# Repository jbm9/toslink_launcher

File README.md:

# TOSLink Launcher

Author: <josh@joshisanerd.com>

License: CC0 / Public Domain

This is a quick-and-dirty PCB mounted TOSLink launcher, which can
couple an SMD LED into a TOSLINK optical cable.  The project includes
both the FreeCAD model and a KiCad demo project (which you can pull
the library/module/STP file out of and into your own setup to use
these.)

There is also an included STL file, but see below on the settings it
was printed with.

## Background
 
TOSLink is a really handy fiber optic cable: you can buy them easily,
reasonably cheaply, and in various lengths.  They are meant for audio,
but they're just flexible lightpipes at the end of the day.

You can buy TOSLink connectors that solder onto PCBs, but they only
come with red LEDs (which is used in the audio application).  If you
want to put arbitrary colors through them, it gets complicated.  So, I
decided to make a little connector that would let me mount a TOSLink
cable over an arbitrary surface mount LED.

## Limitations of included STL file

The STL included here assumes that your printer needs 0.2mm of
fudge-factor on each side to get good results on interior holes.  This
has been the case on both of my FDM printers, but it's probably going
to be suboptimal on SLA (or a particularly well-tuned FDM printer).

It is designed to put the end of the fiber cable 0.7mm above the
surface it's bolted down to.

## Mounting this on a PCB

The mounting arrangement for this is two holes 17mm apart.  I
recommend using 5mm drill hits for these, as you will need to align
the fiber optics perfectly with the LED underneath it.  To do this,
you want to move the connector around a little after it's mounted to
the PCB.  Putting M3 screws through a 5mm hole lets you move up to 1mm
in any direction from center, which should be good enough.

The recommended PCB footprint is an 8mm circle around those M5s, and a
13mm circle about your LED.  (I never claimed this was a
space-efficient footprint…)

## The KiCad demo project

There is a KiCad demo project in toslink_launcher_test.  Opening this
up in KiCad, then going to pcbnew, you should be able to do a 3D view
and see the parts rendered there.

The KiCad demo project includes a separate README.txt which describes
how to import all this into your own KiCad.

## The FreeCAD model

The model was developed in Ubuntu 20.04's distribution of FreeCAD, so
it's an ancient v0.18.4 file.  Apologies if it doesn't actually open
properly in newer versions.

This is a spreadsheet-driven FreeCAD file: if you need to adjust the
squeeze-out fudge factor, or the height of the LED, etc, you can open
the Spreadsheet in the file, tweak the values in that spreadsheet
(don't forget to include “mm” or FreeCAD will have a pedantic little
fit), and it should update the model.  You can then Activate the
“TOSLink Launcher001” Body object by double-clicking on it, and then
File > Export, and type in “toslink_launcher_foo.stl” (you also need
to add the STL there, FreeCAD's great).

This is also a reasonable starting point for the TOSLink connector;
there are precious few models using it, so hopefully this is a good
jumping-off point for anyone else who wants to use these cables for
alternate purposes.

## Further support

Please find someone to assist you with this: unfortunately, I don't
really have the time to help people with it.  This project is being
released more as a starting point for others than as a product in and
of itself.

## Contents:

* README.md: this file
* toslink_launcher.FCStd: FreeCAD v0.18.4 model
* toslink_launcher_v3.stl: STL of the actual launcher
* toslink_launcher_test/: KiCad demo project for the launcher
* imgs/: Images.

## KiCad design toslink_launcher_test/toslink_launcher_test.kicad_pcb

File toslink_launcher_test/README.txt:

# TOSLINK Launcher Example:$

Released: 2021-10-18

Author: Josh Myer <josh@joshisanerd.com}

This is a demo of the KiCad library/module/STP for the TOSLink Launcher.

## Smoke test

You should be able to open this project and use the 3D viewer on the PCB.
This demonstrates that you've got all the pieces together, and can use
them once you get them into your project in KiCad.

## Using the TOSLink Launcher in your project

To use this in your own project, just copy the library, module (the 
toslink_launcherjpretty directory), and the STP file into your project
directory.  You'll need to add them in your project, but hopefully you
won't need to reassociate the 3d model.  If you do, see below.

You need to do a few steps for this:
* Add the library (symbols) to  the project (in eeschema)
* Add the module (footprints) to the project (in pcbnew)
* Add the symbol for the launcher to your schematic
* Associate that symbol with the footprint in the association dialog

That should get it into your PCB.  It's just like adding mounting holes, but
with a custom library.

## Installing the TOSLink Launcher on finished PCBs

Once you have these on the PCB, you'll need 2 M3 screws and nuts for each
launcher you're using.  You should also use washers, but they are optional
for testing things out.  Screw the launcher down very gently, so that it can
still float around a bit.  Then, attach a TOSLINK fiber optic cable to your
 connector and turn the LED on.  You will then need to "float" the launcher
around until you get maximum brightness on the other side.  Then, very
carefully, tighten down the screws to lock it in place there.  Personally, I
usually need to leave the LED on so I can watch the intensity during this
particular process, as it's easy to move the cable ever-so-slightly off of the
optical axis, and dim the light a lot.

## Reassociating the 3D model for preview

If you do need to reassociate the 3d model with the footprint, go into the
footprint editor, edit the toslink_launcher footprint, and then go up to
Edit > Footprint Properties, then the 3D Settings tab and use the little
Folder icon to add the file with the second-least-helpful file chooser.
If it's any consolation, other parts of KiCad make you use the absolute
worst file chooser, so it could be worse?

Once you've done this, you'll need to update the foolprints in pcbnew.
To do that, go to Tools > Update footprints from library, then hit Apply.
This should re-load the footprints from the module, and get the new path
into the file.

## Further assistance

I can't help you with any of the above, but hopefully this is enough context
that you can find tutorials or a person that can help you in your language.

I hope this helps you make lots of neat stuff!

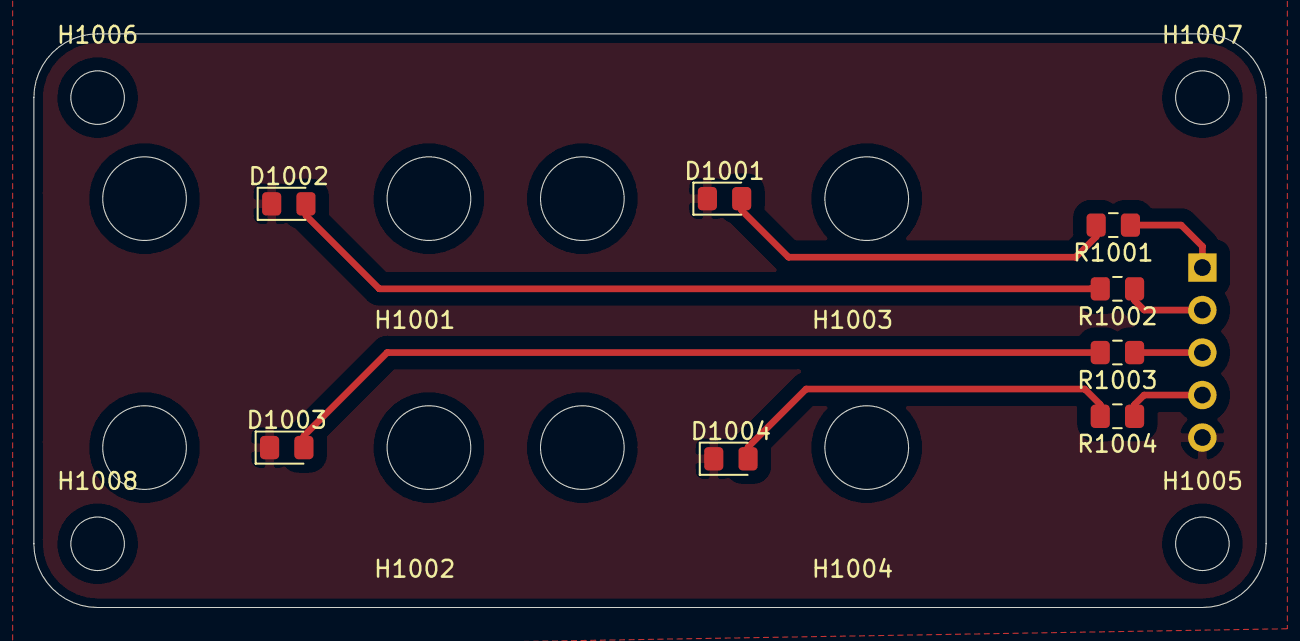
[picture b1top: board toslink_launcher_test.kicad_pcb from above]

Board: 2 copper layers, 73.7 x 34.3 mm, 17 parts (1 on the bottom side), 9 nets.

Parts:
D1001, D1002, D1003, D1004: LED; LED_0805_2012Metric_Pad1.15x1.40mm_HandSolder
H1001, H1002, H1003, H1004: toslink_launcher
H1005, H1006, H1007, H1008: MountingHole; MountingHole_3.2mm_M3_ISO14580
J1001: Conn_01x05; PinHeader_1x05_P2.54mm_Vertical
R1001, R1002, R1003, R1004: R_Small; R_0805_2012Metric_Pad1.15x1.40mm_HandSolder

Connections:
GND: D1001.1, D1002.1, D1003.1, D1004.1, J1001.5
unnamed: D1001.2, R1001.2
unnamed: D1002.2, R1002.2
unnamed: D1003.2, R1003.2
unnamed: D1004.2, R1004.2
unnamed: J1001.1, R1001.1
unnamed: J1001.2, R1002.1
unnamed: J1001.3, R1003.1
unnamed: J1001.4, R1004.1

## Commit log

2021-10-19 Adds empty README
2021-10-19 Collecting the various project files into a single git repo and releasing it
2021-10-19 README.md: adds a preview image of the test PCB

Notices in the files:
toslink_launcher_test/toslink_launcher_test.kicad_pcb:
Released under a CC0 license
